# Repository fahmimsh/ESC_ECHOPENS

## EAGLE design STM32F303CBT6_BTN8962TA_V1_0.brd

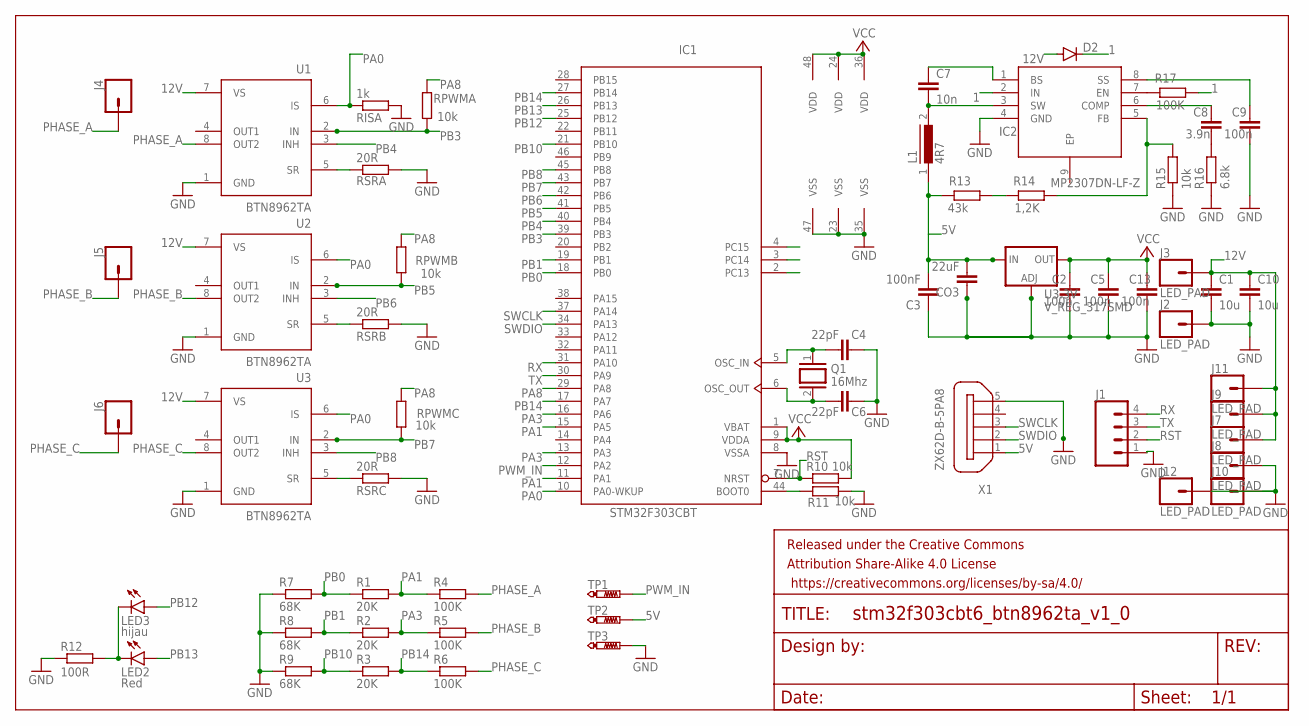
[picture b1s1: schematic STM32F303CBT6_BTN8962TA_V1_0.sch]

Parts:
C1, C10: 10u; C1206K
C2, C5, C9, C13: 100n; C0603K
C3: 100nF; C0805
C4, C6: 22pF; C0805
C7: 10n; C0603K
C8: 3.9n; C0603K
CO3: 22uF; C0805
D2: DIODE-SOD80C; SOD80C
FRAME1: FRAME-LETTER; CREATIVE_COMMONS
IC1: STM32F303CBT; LQFP48
IC2: MP2307DN-LF-Z; SOIC127P600X170-9N
J1: CONN_04SMD2; JST04_1MM_RA
J2, J3, J7, J8, J9, J10, J11, J12: LED_PAD; CIRCULARPAD
J4, J5, J6: CONN_01SNAP-MALE; SNAP-MALE
L1: 4R7; DR74
LED2: Red; CHIPLED_0805
LED3: hijau; CHIPLED_0805
Q1: 16Mhz; QS
R1, R2, R3: 20K; R0805
R4, R5, R6: 100K; R0805
R7, R8, R9: 68K; R0805
R10, R11, R15: 10k; R0603
R12: 100R; R0603
R13: 43k; R0603
R14: 1,2K; R0603
R16: 6.8k; R0603
R17: 100K; R0603
RISA: 1k; R0805
RPWMA: 10k; R0805
RPWMB: 10k; R0805
RPWMC: 10k; R0805
RSRA: 20R; R0805
RSRB: 20R; R0805
RSRC: 20R; R0805
TP1, TP2, TP3: PTR1TP15SQ; TP15SQ
U1, U2, U3: BTN8962TA; TO127P1500X440-8N-1
U3.3V: V_REG_317SMD; SOT223
X1: ZX62D-B-5PA8

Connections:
1: D2.C, IC2.2 (IN), R17.2
5V: C3.2, CO3.2, L1.1, R13.1, TP2.TP, U3.3V.3 (IN), X1.1
12V: C1.1, C10.1, D2.A, J3.P$1, J3.P$2, J7.P$1, J7.P$2, J9.P$1, J9.P$2, J11.P$1, J11.P$2, U1.7 (VS), U2.7 (VS), U3.7 (VS)
GND: C1.2, C2.2, C3.1, C4.1, C5.2, C6.1, C9.2, C10.2, C13.2, CO3.1, IC1.8 (VSSA), IC1.23 (VSS), IC1.35 (VSS), IC1.47 (VSS), IC2.4 (GND), J1.1, J2.P$1, J2.P$2, J8.P$1, J8.P$2, J10.P$1, J10.P$2, J12.P$1, J12.P$2, R7.1, R8.1, R9.1, R11.2, R12.1, R15.1, R16.1, RISA.2, RSRA.2, RSRB.2, RSRC.2, TP3.TP, U1.1 (GND), U2.1 (GND), U3.1 (GND), U3.3V.1 (ADJ), X1.5
unnamed: C4.2, IC1.5 (OSC_IN), Q1.1
unnamed: RSRA.1, U1.5 (SR)
unnamed: C7.1, IC2.1 (BS)
unnamed: C7.2, IC2.3 (SW), L1.2
unnamed: C6.2, IC1.6 (OSC_OUT), Q1.2
unnamed: RSRB.1, U2.5 (SR)
unnamed: LED2.C, LED3.C, R12.2
unnamed: RSRC.1, U3.5 (SR)
unnamed: IC1.44 (BOOT0), R11.1
unnamed: R13.2, R14.1
unnamed: IC2.5 (FB), R14.2, R15.2
unnamed: C8.2, R16.2
unnamed: C8.1, IC2.6 (COMP)
unnamed: IC2.7 (EN), R17.1
unnamed: C9.1, IC2.8 (SS)
PA0: IC1.10 (PA0-WKUP), RISA.1, U1.6 (IS), U2.6 (IS), U3.6 (IS)
PA1: IC1.11 (PA1), IC1.15 (PA5), R1.2, R4.1
PA3: IC1.13 (PA3), IC1.16 (PA6), R2.2, R5.1
PA8: IC1.29 (PA8), RPWMA.2, RPWMB.2, RPWMC.2
PB0: IC1.18 (PB0), R1.1, R7.2
PB1: IC1.19 (PB1), R2.1, R8.2
PB3: IC1.39 (PB3), RPWMA.1, U1.2 (IN)
PB4: IC1.40 (PB4), U1.3 (INH)
PB5: IC1.41 (PB5), RPWMB.1, U2.2 (IN)
PB6: IC1.42 (PB6), U2.3 (INH)
PB7: IC1.43 (PB7), RPWMC.1, U3.2 (IN)
PB8: IC1.45 (PB8), U3.3 (INH)
PB10: IC1.21 (PB10), R3.1, R9.2
PB12: IC1.25 (PB12), LED3.A
PB13: IC1.26 (PB13), LED2.A
PB14: IC1.17 (PA7), IC1.27 (PB14), R3.2, R6.1
PHASE_A: J4.2, R4.2, U1.8 (OUT2)
PHASE_B: J5.2, R5.2, U2.8 (OUT2)
PHASE_C: J6.2, R6.2, U3.8 (OUT2)
PWM_IN: IC1.12 (PA2), TP1.TP
RST: IC1.7 (NRST), J1.2, R10.1
RX: IC1.31 (PA10), J1.4
SWCLK: IC1.37 (PA14), X1.3
SWDIO: IC1.34 (PA13), X1.2
TX: IC1.30 (PA9), J1.3
VCC: C2.1, C5.1, C13.1, IC1.1 (VBAT), IC1.9 (VDDA), IC1.24 (VDD), IC1.36 (VDD), IC1.48 (VDD), R10.2, U3.3V.2 (OUT)

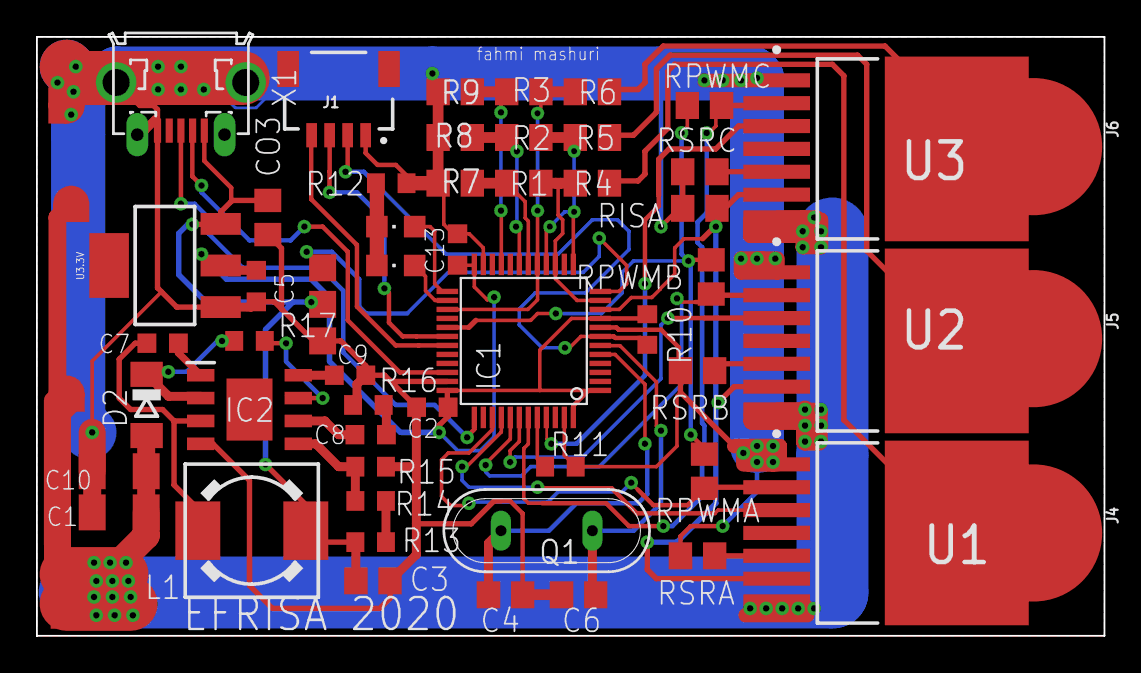
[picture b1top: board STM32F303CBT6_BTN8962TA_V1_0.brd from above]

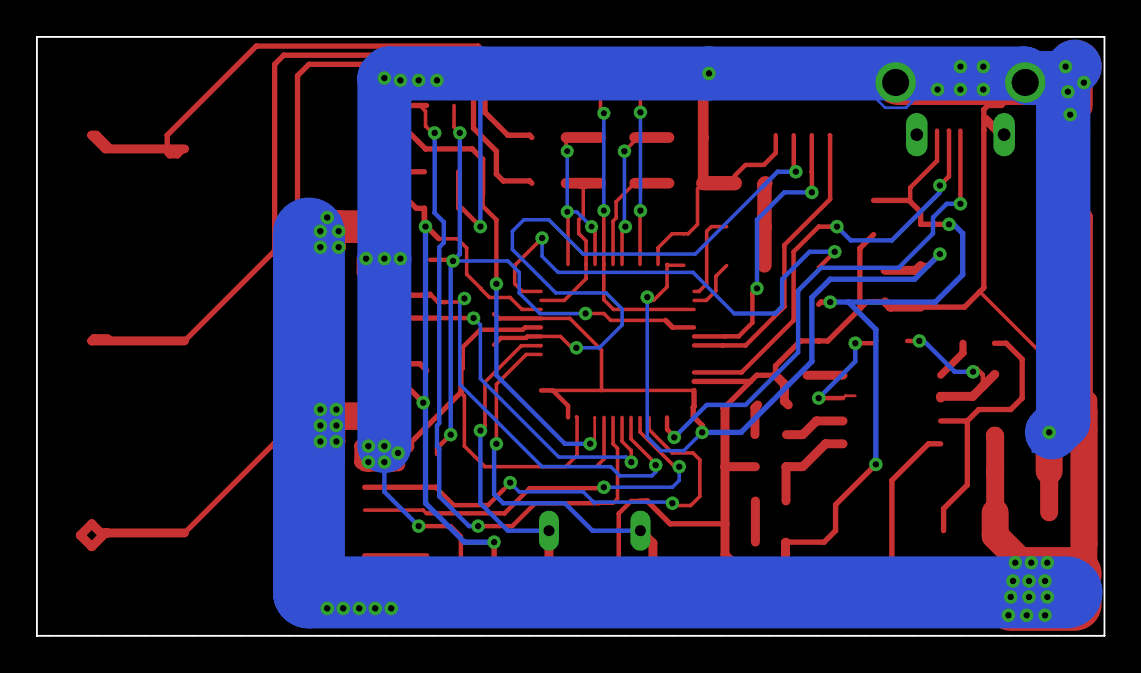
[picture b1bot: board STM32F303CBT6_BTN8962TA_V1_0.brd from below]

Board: 2 copper layers, 59.3 x 33.3 mm, 64 parts (2 on the bottom side), 45 nets.

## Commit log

2020-10-04 upload1

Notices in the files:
parts and their libraries:
SparkFun-PowerIC: Licensing: CC v3.0 Share-Alike You are welcome to use this library for commercial purposes.
SparkFun-Connectors: Licensing: Creative Commons ShareAlike 4.0 International - https://creativecommons.org/licenses/by-sa/4.0
SparkFun-Aesthetics: Released under the Creative Commons
